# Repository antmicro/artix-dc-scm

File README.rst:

============
Artix DC-SCM
============

Copyright (c) 2020-2021 `Antmicro <https://www.antmicro.com>`_

.. image:: https://img.shields.io/badge/View%20on-Antmicro%20Open%20Source%20Portal-332d37?style=flat-square
   :target: https://opensource.antmicro.com/projects/artix-dc-scm 

.. figure:: img/artix-dc-scm.jpg

Overview
--------

This repository contains design files for an open-source Baseboard Management Controller (BMC) module based on the Xilinx Artix-7 FPGA family, designed in accordance with the Data Center Secure Control Module (DC-SCM) specification of Open Compute Project (OCP).

The design files were prepared in KiCad.
This design is complete and now undergoing bringup.

Repository structure
--------------------

The main repository directory contains KiCad PCB project files, a LICENSE and README.
The remaining files are stored in the following directories:

* ``lib`` - contains the component libraries
* ``img`` - contains graphics for this README

Key Features
------------

* Artix-7 FPGA - XC7A100T-FGG484
* DC-SCI standard 168-pin 4C+ edge connector
* On-board DDR3 DRAM (AS4C256M16D3) and eMMC (MTFC16GAPALNA-AIT)
* 4x SPI FLASH memory
* Gigabit Ethernet over KSZ9031RNXCA PHY
* JTAG connector
* Host and client USB (over USB3300-EZK-TR PHY)
* M.2 NVMe interface
* 13x I2C buses, 4x I3C buses
* 2x UART 
* SPI connector
* RoT module connector
* TPM SPI connector

Block diagram
-------------

.. figure:: img/artix-dc-scm-diagram.png

License
=======

`Apache-2.0 <LICENSE>`_

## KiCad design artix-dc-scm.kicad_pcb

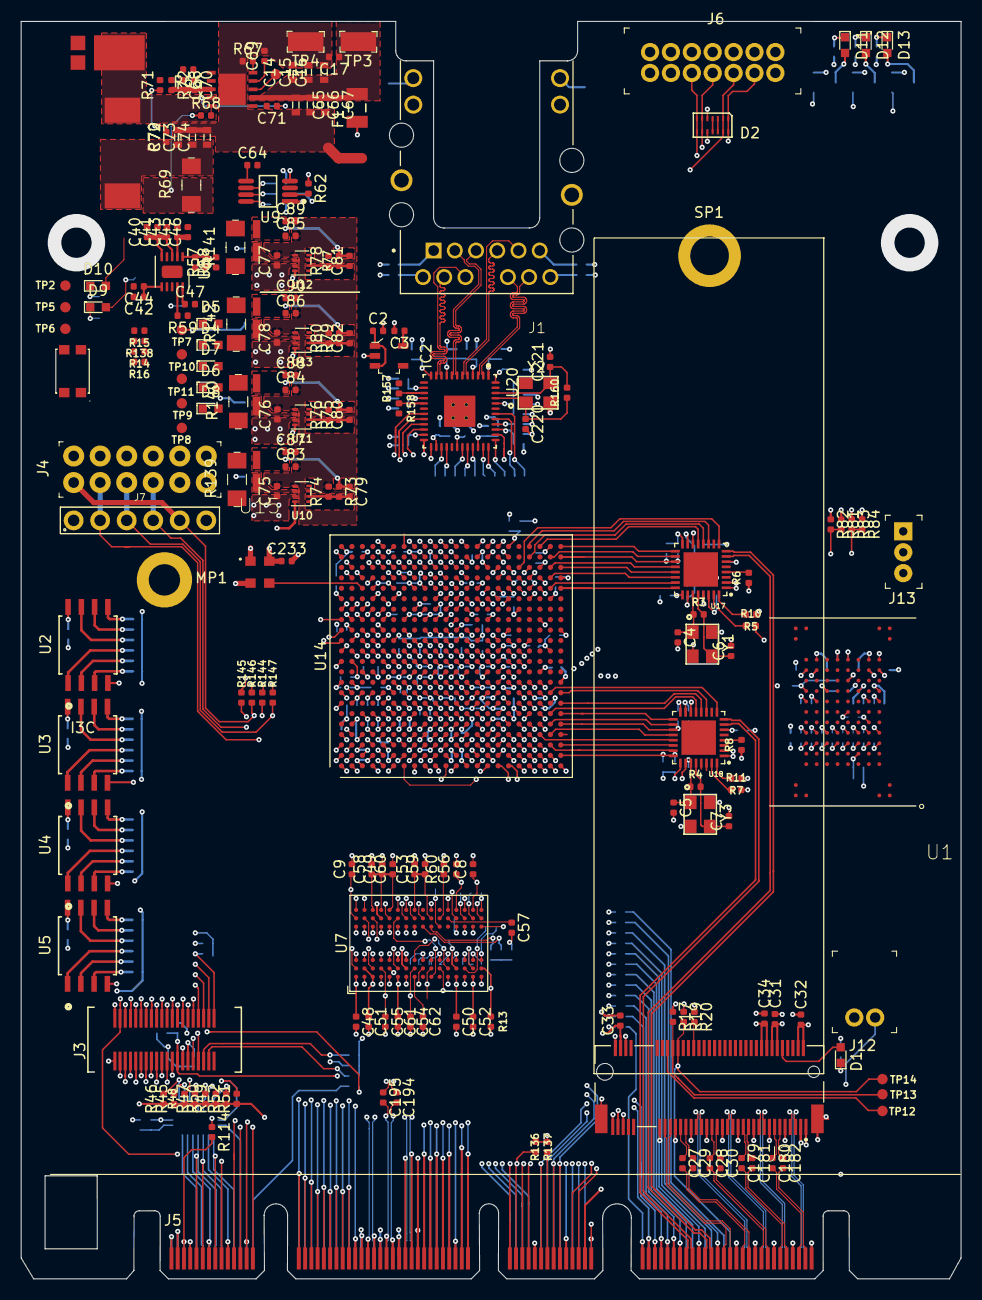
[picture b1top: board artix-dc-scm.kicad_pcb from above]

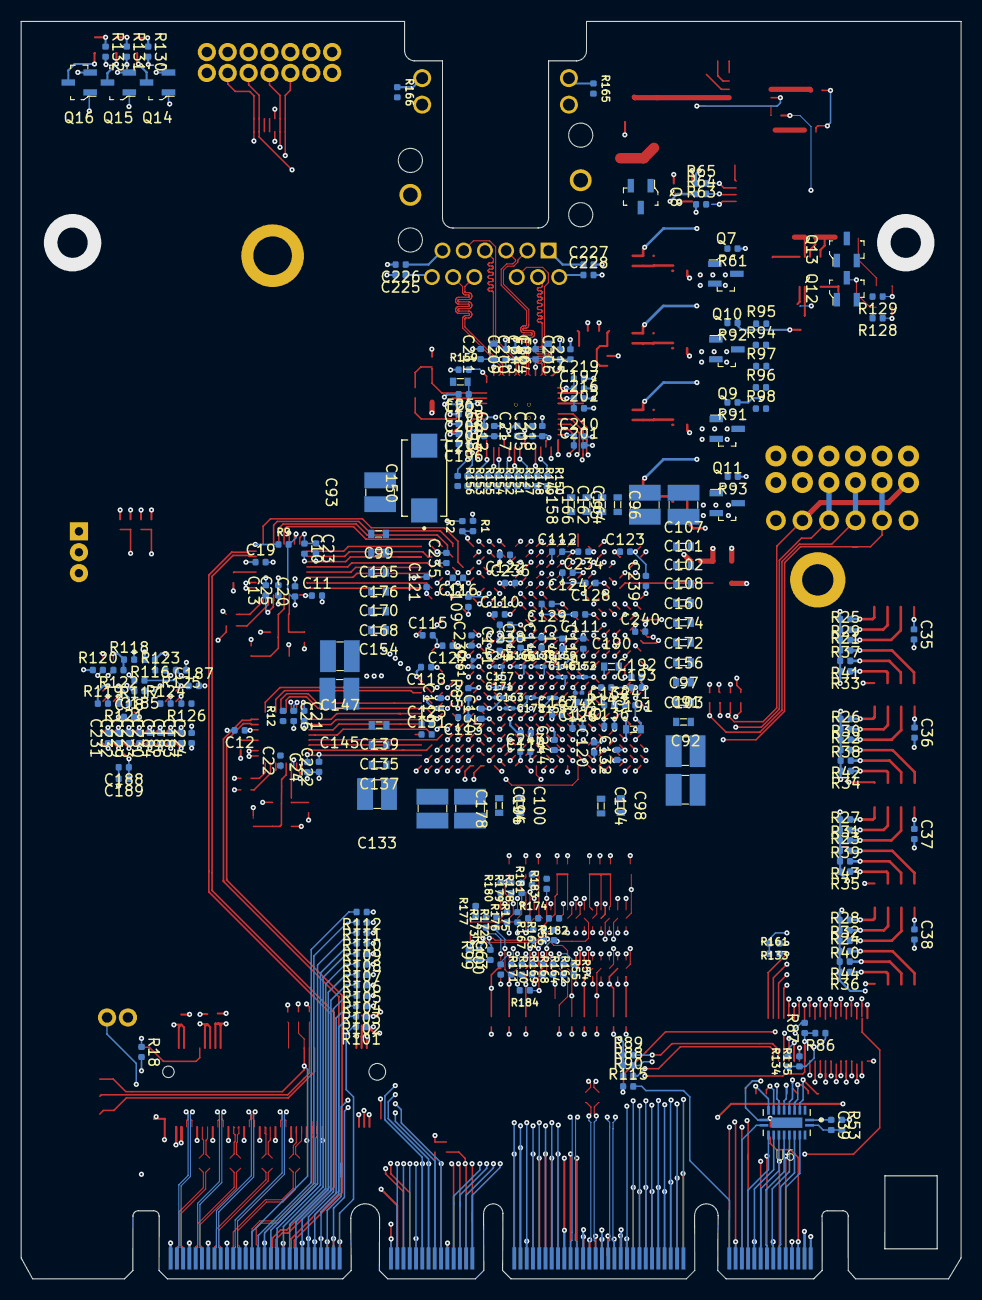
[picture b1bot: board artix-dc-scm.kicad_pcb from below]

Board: 8 copper layers, 90.0 x 120.4 mm, 502 parts (293 on the bottom side), 427 nets.

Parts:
C1: C_1n_0402; 0402-res
C2, C3: C_1u_0402; 0402-cap
C4, C5, C6, C7: C_12p_0402; 0402-cap
C8, C9, C35, C36, C37, C38, C49, C50, C51, C52, C53, C54, C55, C56, C58, C59, C60, C61, C109, C110, C111, C112, C113, C114, C115, C116, C117, C118, C119, C120, C121, C122, C123, C124, C125, C126, C127, C128, C129, C130, C131, C132, C140, C141, C143, C144, C148, C167, C197, C201, C202, C204, C205, C234, C235, C236, C237, C238, C239, C240, C243, C244: C_470n_0402; 0402-cap
C10, C11, C12, C13, C18, C19, C20, C21, C22, C24, C25, C26, C27, C28, C29, C30, C39, C42, C44, C45, C46, C57, C62, C63, C71, C134, C136, C179, C180, C181, C182, C186, C187, C189, C192, C193, C194, C195, C203, C223, C224, C225, C226, C227, C228, C229, C230, C231, C232, C233, C241: C_100n_0402; 0402-cap
C14, C15, C16: C_10u_25V_0603; 0603-cap
C17: C_100n_0402_16V; 0402-cap
C23, C48, C188, C196, C198, C199, C200, C206, C222: C_4u7_0402; 0402-cap
C31, C32, C33, C34, C40, C41, C43, C47, C75, C76, C77, C78, C83, C84, C85, C86, C87, C88, C89, C90: C_10u_0402; 0402-cap
C64, C69, C207, C208, C209, C210, C211, C212, C213, C214, C215, C216, C217, C218, C219: C_10n_0402; 0402-cap
C65, C66, C67: C_2u2_0603_25V; 0603-cap
C68: C_4n7_0402; 0402-cap
C70: C_47p_0402; 0402-cap
C72, C73, C74: C_47u_0603; 0603-cap
C79, C80, C81, C82: C_120p_0402; 0402-res
C91, C92, C93, C94, C95, C96, C133, C147, C178: C_47u_1210; 1210-cap
C97, C98, C99, C100, C101, C102, C103, C104, C105, C106, C107, C108, C135, C137, C139, C154, C156, C158, C160, C162, C164, C166, C168, C170, C172, C174, C176, C190, C191: C_4u7_0603; 0603-cap
C138, C142, C146, C152, C153, C157, C159, C161, C163, C165, C171, C175, C242: C_470n_0402; 0201-res
C145: C_100u_1210; 1210-cap
C150: C_330u_KEMET_D; KEMET_D
C183, C184, C185: C_2u2_0402; 0402-cap
C220, C221: C_22p_0402; 0402-cap
D1: KP-1608CGCK; LED_0603
D2: TPD6E05U06
D3: PDS760-13
D4, D5, D6, D7, D8, D9, D10, D11, D12, D13: LG_L29K-G2J1-24-Z; LED_0603
F1: 0466003.NR; 1206-Fuse-Littelfuse-0466-0-0-MFG
FB4, FB5, FB6: BLM18PG121SN1D; 0603-res
IC1: TPS54561; WSON-10_4x4
IC2: TLV73312PDBVT; SOT-23-5
J1: L834-1G1T-S7; BEL_L834-1G1T-S7
J2: 1-2199230-6
J3: 529910408
J4: M20-7830642; PinHeader_6x2_P2.54mm_Vertical
J5: SFF-TA-1002-4C+
J6: 0878311420; PinHeader_2x7_P2mm_Drill1mm
J7: 61300611121
J12: S2B-PH-K-S_LF__SN_; PinHeader_1x2_P2mm_Drill1mm_RA
J13: 62000311121
L1: WE_7447798720
L2, L3, L4, L5: IHLP1212AEERR47M11; IHLP-1212AE
MP1: PCB_Spacer_M2; 9774030243R
PROG_B1: KMR2; SW_SPST_4.2x2.8
Q7, Q8, Q9, Q10, Q11, Q12, Q13, Q14, Q15, Q16: 2N7002; SOT-23-3
R1, R2, R6, R8, R25, R26, R27, R28, R62, R63, R64, R65, R94, R95, R96, R97, R98, R128, R129, R130, R131, R132: R_1k_0402; 0402-res
R3, R4: R_1M5_0402; 0402-res
R5, R7: R_12k_0402; 0402-res
R9, R10, R11, R12, R14, R15, R16, R81, R82, R83, R84, R101, R102, R103, R104, R105, R106, R107, R108, R109, R110, R111, R112, R114, R115, R136, R137, R138, R144, R145, R146, R147, R161: R_0R_0402; 0402-res
R13, R21, R22, R23, R24, R85, R89, R90, R134, R135: R_4k7_0402; 0402-res
R17, R19, R20, R29, R30, R31, R32, R33, R34, R35, R36, R37, R38, R39, R40, R41, R42, R43, R44, R57, R58, R59, R61, R91, R92, R93, R116, R117, R118, R119, R120, R121, R122, R123, R124, R125, R126: R_10k_0402; 0402-res
R18: R_330R_0402; 0402-res
R45, R46, R47, R48, R49, R50, R51, R52: R_357k_0402; 0402-res
R53, R75: R_200k_0402; 0402-res
R54, R55, R56, R99, R100, R162, R163, R164, R167, R168, R169, R170, R171, R172, R173, R174, R175, R176, R177, R178, R179, R180, R181, R182, R183, R184: R_51R_0402; 0402-res
R60: R_240R_0402; 0402-res
R66: R_16k9_0402; 0402-res
R67: R_243k_0402; 0402-res
R68, R74, R76, R78, R80: R_100k_0402; 0402-res
R69, R139, R140, R141, R142: R_0R_1206; 1206-res
R70: R_49R9_0402; 0402-res
R71: R_53k6_0402; 0402-res
R72, R127, R148, R149, R150, R151, R152, R153, R154, R155, R156, R157, R158: R_10k2_0402; 0402-res
R73: R_453k_0402; 0402-res
R77: R_66k5_0402; 0402-res
R79: R_124k_0402; 0402-res
R86, R87, R143: R_100R_0402; 0402-res
R88: R_200R_0402; 0402-res
R133: R_2k2_0402; 0402-res
R159: R_12k1_0402; 0402-res
R160: R_1M8_0402; 0402-res
R165, R166: R_220R_0402; 0402-res
SP1: 9774025151
TP1, TP2, TP5, TP6, TP7, TP8, TP9, TP10, TP11, TP12, TP13, TP14: TP_SMD1MM; Testpoint_smd_1mm
TP3, TP4: RCW-0C; PROBE_PAD_1206
U1: MTFC16GAPALNA-AIT; BGA100CP100_17X10_1800X1400X140B46N
U2, U3, U4, U5: W25Q32JVSSIQ_TR; W25Q32JVSSIQ
U6: NVT2008DQ,115; QFN50P250X450X100-21N
U7: AS4C256M16D3; BGA-96_9.0x13.0mm_Layout2x3x16_P0.8mm
U8: TPS51200DRC; VSON-10-1EP_3x3mm
U9: LM3881MME_NOPB; VSSOP8-Texas_Instruments-DGK0008A
U10, U11, U12, U13: TPS62823DLCT; QFN-8_2x1mm
U14: XC7A100T-FGG484; Xilinx_FGG484
U15: AMJMEFB-100.0000T; AMJMEFB
U17, U18: USB3300-EZK-TR; QFN50P500X500X100-33N
U20: KSZ9031RNXCA; QFN-48-Microchip-QFN77-48LD-PL-2
Y1, Y3: TSX-3225; KX-7
Y2: ABM8G-25.000MHZ-18-D2Y-T; KX-7

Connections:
3V0_BAT: J5.B41, J12.1
/DDR3/DDR3_VTT: C40.1, C41.1, C43.1, R54.2, R55.2, R56.2, R162.2, R163.2, R164.2, R167.2, R168.2, R169.2, R170.2, R171.2, R172.2, R173.2, R174.2, R175.2, R176.2, R177.2, R178.2, R179.2, R180.2, R181.2, R182.2, R183.2, R184.2, U8.3, U8.5
/Ethernet/AVDDH: C206.1, C211.1, C215.1, FB4.2, U20.1, U20.12
/Ethernet/AVDDL: C200.1, C204.1, C209.1, C213.1, FB6.1, U20.4, U20.9
/Ethernet/AVDDL_PLL: C199.1, C203.1, C208.1, FB5.1, U20.44
/Ethernet/ETH1_N: J1.10, U20.3
/Ethernet/ETH1_P: J1.11, U20.2
/Ethernet/ETH2_N: J1.5, U20.6
/Ethernet/ETH2_P: J1.4, U20.5
/Ethernet/ETH3_N: J1.2, U20.8
/Ethernet/ETH3_P: J1.3, U20.7
/Ethernet/ETH4_N: J1.9, U20.11
/Ethernet/ETH4_P: J1.8, U20.10
/Ethernet/ETH_LED1: R157.1, U20.15
/Ethernet/ETH_LED2: R158.1, U20.17
/Interfaces/1V0_EN: C39.2, R53.2, U6.2, U6.20
/Interfaces/PCIE_BMC_TX_C_N: C194.1, U14.A4
/Interfaces/PCIE_BMC_TX_C_P: C195.1, U14.B4
/PCIe-connector/NVME_LED: D1.2, J2.10
/PCIe-connector/PCIE_HPM_TX0_C_N: C29.1, J2.47
/PCIe-connector/PCIE_HPM_TX0_C_P: C27.1, J2.49
/PCIe-connector/PCIE_HPM_TX1_C_N: C30.1, J2.35
/PCIe-connector/PCIE_HPM_TX1_C_P: C28.1, J2.37
/PCIe-connector/PCIE_HPM_TX2_C_N: C181.1, J2.23
/PCIe-connector/PCIE_HPM_TX2_C_P: C179.1, J2.25
/PCIe-connector/PCIE_HPM_TX3_C_N: C182.1, J2.11
/PCIe-connector/PCIE_HPM_TX3_C_P: C180.1, J2.13
/Power supply/1V0_PG: Q7.1, R61.2, U12.8
/Power supply/1V8_PG: Q9.1, R91.2, U11.8
/Power supply/1V35_PG: Q10.1, R92.2, U13.8
/Power supply/2V5_PG: Q11.1, R93.2
/Power supply/PWR_EN: Q8.1, R62.2, U9.2
/Power supply/VCCAUX_EN: R15.2, R64.2, U9.7
/Power supply/VCCINT_EN: R16.2, R63.2, U9.8
/Power supply/VCCIO_EN: R14.2, R65.2, R138.2, U9.6
CHASI#: J5.A54, R110.2
CHASI#_R: R110.1, U14.Y3
DBP_PRDY_N: J5.A50, R106.2
DBP_PRDY_N_R: R106.1, U14.W2
DBP_PREQ_N: J5.A49, R105.2
DBP_PREQ_N_R: R105.1, U14.V2
DDR3_A0: R168.1, U7.N3, U14.M2
DDR3_A1: R175.1, U7.P7, U14.M5
DDR3_A2: R169.1, U7.P3, U14.M3
DDR3_A3: R167.1, U7.N2, U14.M1
DDR3_A4: R178.1, U7.P8, U14.L6
DDR3_A5: R172.1, U7.P2, U14.P1
DDR3_A6: R179.1, U7.R8, U14.N3
DDR3_A7: R170.1, U7.R2, U14.N2
DDR3_A8: R180.1, U7.T8, U14.M6
DDR3_A9: R171.1, U7.R3, U14.R1
DDR3_A10: R183.1, U7.L7, U14.L5
DDR3_A11: R176.1, U7.R7, U14.N5
DDR3_A12: R174.1, U7.N7, U14.N4
DDR3_A13: R173.1, U7.T3, U14.P2
DDR3_A14: R177.1, U7.T7, U14.P6
DDR3_BA0: R163.1, U7.M2, U14.L3
DDR3_BA1: R181.1, U7.N8, U14.K6
DDR3_BA2: R164.1, U7.M3, U14.L4
DDR3_CAS: R55.1, U7.K3, U14.K3
DDR3_CKE: R182.1, U7.K9, U14.J6
DDR3_CLK_N: R100.2, U7.K7, U14.P4
DDR3_CLK_P: R99.2, U7.J7, U14.P5
DDR3_CS: R184.1, U7.L2
DDR3_DM0: U7.E7, U14.G3
DDR3_DM1: U7.D3, U14.F1
DDR3_DQ0: U7.E3, U14.G2
DDR3_DQ1: U7.F7, U14.H4
DDR3_DQ2: U7.F2, U14.H5
DDR3_DQ3: U7.F8, U14.J1
DDR3_DQ4: U7.H3, U14.K1
DDR3_DQ5: U7.H8, U14.H3
DDR3_DQ6: U7.G2, U14.H2
DDR3_DQ7: U7.H7, U14.J5
DDR3_DQ8: U7.D7, U14.E3
DDR3_DQ9: U7.C3, U14.B2
DDR3_DQ10: U7.C8, U14.F3
DDR3_DQ11: U7.C2, U14.D2
DDR3_DQ12: U7.A7, U14.C2
DDR3_DQ13: U7.A2, U14.A1
DDR3_DQ14: U7.B8, U14.E2
DDR3_DQ15: U7.A3, U14.B1
DDR3_DQS0_N: U7.G3, U14.J2
DDR3_DQS0_P: U7.F3, U14.K2
DDR3_DQS1_N: U7.B7, U14.D1
DDR3_DQS1_P: U7.C7, U14.E1
DDR3_ODT: R56.1, U7.K1, U14.K4
DDR3_RAS: R54.1, U7.J3, U14.J4
DDR3_RESET: R13.1, U7.T2, U14.G1
DDR3_VREF: C42.1, C44.1, C57.1, C62.1, U7.H1, U7.M8, U8.6
DDR3_WE: R162.1, U7.L3, U14.L1
DONE: Q13.1, R88.2, TP2.1, U14.G11
ESPI_ALERT_N: J5.B3, U14.H18
ESPI_CLK: J5.B1, U14.L18
ESPI_CS0_N: J5.B2, U14.K18
ESPI_CS1_N: J5.B9, U14.G15
ESPI_IO0: J5.B5, U14.K17
ESPI_IO1: J5.B6, U14.M16
ESPI_IO2: J5.B7, U14.K16
ESPI_IO3: J5.B8, U14.L16
ESPI_RESET_N: J5.B4, U14.M17
ETH_INT_N: U14.N20, U20.38
ETH_MDC: R154.1, U14.N22, U20.36
ETH_MDIO: R155.1, U14.M20, U20.37
ETH_~RESET: R156.1, U14.N18, U20.42
GCLK100: U14.C18, U15.3
GND: C1.2, C2.2, C3.2, C4.2, C5.2, C6.2, C7.2, C8.2, C9.2, C10.2, C11.2, C12.2, C13.2, C14.2, C15.2, C16.2, C17.2, C18.2, C19.2, C20.2, C21.2, C22.2, C23.2, C24.2, C25.2, C26.2, C31.2, C32.2, C33.2, C34.2, C35.2, C36.2, C37.2, C38.2, C39.1, C40.2, C41.2, C42.2, C43.2, C44.2, C45.2, C46.2, C47.2, C48.2, C49.2, C50.2, C51.2, C52.2, C53.2, C54.2, C55.2, C56.2, C57.2, C58.2, C59.2, C60.2, C61.2, C62.2, C63.1, C64.2, C65.2, C66.2, C67.2, C68.2, C69.2, C70.2, C72.2, C73.2, C74.2, C75.2, C76.2, C77.2, C78.2, C83.2, C84.2, C85.2, C86.2, C87.2, C88.2, C89.2, C90.2, C91.2, C92.2, C93.2, C94.2, C95.2, C96.2, C97.2, C98.2, C99.2, C100.2, C101.2, C102.2, C103.2, C104.2, C105.2, C106.2, C107.2, C108.2, C109.2, C110.2, C111.2, C112.2, C113.2, C114.2, C115.2, C116.2, C117.2, C118.2, C119.2, C120.2, C121.2, C122.2, C123.2, C124.2, C125.2, C126.2, C127.2, C128.2, C129.2, C130.2, C131.2, C132.2, C133.2, C134.2, C135.2, C136.2, C137.2, C138.2, C139.2, C140.2, C141.2, C142.2, C143.2, C144.2, C145.2, C146.2, C147.2, C148.2, C150.2, C152.2, C153.2, C154.2, C156.2, C157.2, C158.2, C159.2, C160.2, C161.2, C162.2, C163.2, C164.2, C165.2, C166.2, C167.2, C168.2, C170.2, C171.2, C172.2, C174.2, C175.2, C176.2, C178.2, C183.2, C184.2, C185.2, C186.2, C187.2, C188.2, C189.2, C190.2, C191.2, C192.2, C193.2, C196.2, C197.2, C198.2, C199.2, C200.2, C201.2, C202.2, C203.2, C204.2, C205.2, C206.2, C207.2, C208.2, C209.2, C210.2, C211.2, C212.2, C213.2, C214.2, C215.2, C216.2, C217.2, C218.2, C219.2, C220.2, C221.2, C222.2, C223.2, C224.2, C225.2, C226.2, C227.2, C228.2, C229.2, C230.2, C231.2, C232.2, C233.2, C234.2, C235.2, C236.2, C237.2, C238.2, C239.2, C240.2, C241.2, C242.2, C243.2, C244.2, D2.5, D2.10, D3.A, IC1.8, IC1.11, IC2.2, J1.13, J1.15, J1.S1, J1.S2, J2.1, J2.3, J2.9, J2.15, J2.21, J2.27, J2.33, J2.39, J2.45, J2.51, J2.57, J2.71, J2.73, J2.75, J2.SH1, J2.SH2, J3.1, J4.5, J4.11, J5.A11, J5.A14, J5.A17, J5.A20, J5.A33, J5.A42, J5.A58, J5.A61, J5.A64, J5.A67, J5.A70, J5.B10, J5.B17, J5.B26, J5.B33, J5.B38, J5.B49, J5.B52, J5.B55, J5.B58, J5.B61, J5.B64, J5.B67, J5.B70, J5.OA3, J5.OA4, J5.OA13, J5.OB4, J5.OB7, J5.OB10, J6.1, J6.3, J6.5, J6.7, J6.9, J6.11, J6.13, J7.6, J12.2, J13.3, PROG_B1.2, Q7.2, Q8.2, Q9.2, Q10.2, Q11.2, Q12.2, Q13.2, Q14.2, Q15.2, Q16.2, R2.2, R5.1, R7.1, R13.2, R57.1, R60.2, R67.1, R72.2, R74.2, R76.2, R78.2, R80.2, R82.1, R84.1, R87.2, R159.1, TP4.1, U1.G2, U1.G3, U1.G4, U1.G5, U1.G6, U1.G7, U1.G8, U1.G9, U1.J5, U2.4, U3.4, U4.4, U5.4, U6.1, U7.A9, U7.B1, U7.B3, U7.B9, U7.D1, U7.D8, U7.E1, U7.E2, U7.E8, U7.F9, U7.G1, U7.G8, U7.G9, U7.J2, U7.J8, U7.M1, U7.M9, U7.P1, U7.P9, U7.T1, U7.T9, U8.4, U8.8, U8.11, U9.3, U10.3, U10.5, U11.3, U11.5, U12.3, U12.5, U13.3, U13.5, U14.A2, U14.A3, U14.A5, U14.A7, U14.A9, U14.A11, U14.A12, U14.A22, U14.AA2, U14.AA12, U14.AA22, U14.AB9, U14.AB19, U14.B3, U14.B12, U14.B19, U14.C3, U14.C6, U14.C10, U14.C12, U14.C16, U14.D3, U14.D4, U14.D8, U14.D12, U14.D13, U14.E4, U14.E5, U14.E7, U14.E9, U14.E11, U14.E20, U14.F5, U14.F11, U14.F17, U14.G5, U14.G6, U14.G7, U14.G8, U14.G9, U14.G10, U14.G12, U14.G14, U14.H1, U14.H7, U14.H9, U14.H11, U14.H21, U14.J8, U14.J10, U14.J12, U14.J18, U14.K5, U14.K7, U14.K9, U14.K11, U14.K15, U14.L2, U14.L8, U14.L9, U14.L10, U14.L22, U14.M7, U14.M9, U14.M10, U14.M11, U14.M19, U14.N6, U14.N8, U14.N9, U14.N10, U14.N16, U14.P3, U14.P7, U14.P9, U14.P11, U14.P13, U14.R8, U14.R10, U14.R12, U14.R20, U14.T7, U14.T9, U14.T11, U14.T17, U14.U4, U14.U14, U14.V1, U14.V11, U14.V21, U14.W8, U14.W18, U14.Y5, U14.Y15, U15.2, U17.1, U17.2, U17.33, U18.1, U18.2, U18.33, U20.29, U20.49, Y1.2, Y1.4, Y2.2, Y2.4, Y3.2, Y3.4
HPM_FW_RECOVERY: J5.A43, R101.2
HPM_FW_RECOVERY_R: R101.1, U14.U3
HPM_STBY_RST_N: J5.A46, R102.2
HPM_STBY_RST_N_R: R102.1, U14.U1
I2C[0]_SCL: J5.A1, U14.J16
I2C[0]_SDA: J5.A2, U14.J15
I2C[1]_SCL: J5.A3, U14.L15
I2C[1]_SDA: J5.A4, U14.M15
I2C[2]_SCL: J5.A5, U14.L14
I2C[2]_SDA: J5.A6, U14.J14
I2C[3]_SCL: J5.A7, U14.K14
I2C[3]_SDA: J5.A8, U14.M13
I2C[4]_SCL: J5.A9, U14.K13
I2C[4]_SDA: J5.A10, U14.L13
I2C[5]_SCL: J5.A21, U14.N13
I2C[5]_SDA: J5.A22, U14.N14
I2C[6]_SCL: J5.A23, U14.H13
I2C[6]_SDA: J5.A24, U14.G13
I2C[7]_SCL: J5.A25, U14.F13
I2C[7]_SDA: J5.A26, U14.E13
I2C[8]_SCL: J5.A27, U14.C13
I2C[8]_SDA: J5.A28, U14.C14
I2C[9]_SCL: J5.A29, U14.T5
I2C[9]_SDA: J5.A30, U14.T6
I2C[10]_SCL: J5.A31, U14.U6
I2C[10]_SDA: J5.A32, U14.W6
I2C[11]_SCL: J5.A38, U14.W7
I2C[11]_SDA: J5.A39, U14.W9
I2C[12]_SCL: J5.A40, U14.V8
I2C[12]_SDA: J5.A41, U14.V9
I3C[0]_SCL: J5.OA5, U6.18
I3C[0]_SCL_3V3: R46.2, U6.3, U14.A21
I3C[0]_SDA: J5.OA6, U6.17
I3C[0]_SDA_3V3: R45.2, U6.4, U14.B20
I3C[1]_SCL: J5.OA7, U6.16
I3C[1]_SCL_3V3: R48.2, U6.5, U14.D20
I3C[1]_SDA: J5.OA8, U6.15
I3C[1]_SDA_3V3: R47.2, U6.6, U14.F20
I3C[2]_SCL: J5.OA9, U6.14
I3C[2]_SCL_3V3: R50.2, U6.7, U14.C19
I3C[2]_SDA: J5.OA10, U6.13
I3C[2]_SDA_3V3: R49.2, U6.8, U14.F19
I3C[3]_SCL: J5.OA11, U6.12
I3C[3]_SCL_3V3: R52.2, U6.9, U14.D19
I3C[3]_SDA: J5.OA12, U6.11
I3C[3]_SDA_3V3: R51.2, U6.10, U14.F18
INIT: J3.19, Q12.1, R90.2, TP5.1, U14.U12
IRQ_N: J5.A56, R112.2
IRQ_N_R: R112.1, U14.AB1
JTAG_TCK: D2.13, J5.A34, J6.6, U14.V12
JTAG_TDI: D2.8, J5.A36, J6.10, U14.R13
JTAG_TDO: D2.9, J5.A37, J6.8, U14.U13
JTAG_TMS: D2.14, J5.A35, J6.4, U14.T13
MMC_CLK: R116.2, U1.P6, U14.Y18
MMC_CMD: R118.2, U1.P5, U14.Y19
MMC_DAT0: R119.2, U1.K2, U14.P17
MMC_DAT1: R120.2, U1.N2, U14.W17
MMC_DAT2: R121.2, U1.K3, U14.R18
MMC_DAT3: R122.2, U1.N3, U14.V18
MMC_DAT4: R123.2, U1.N8, U14.U18
MMC_DAT5: R124.2, U1.K8, U14.U17
MMC_DAT6: R125.2, U1.N9, U14.T18
MMC_DAT7: R126.2, U1.K9, U14.R17
MMC_RSTN: R117.2, U1.M5, U14.V19
MODE0: R81.2, R82.2, U14.U11
MODE1: R83.2, R84.2, U14.U10
MODE2: J13.2, U14.U9
NCSI_CLK: J5.B18, U14.B13
NCSI_CRS_DV: J5.B19, U14.A14
NCSI_RXD0: J5.B24, U14.A15
NCSI_RXD1: J5.B25, U14.B15
NCSI_RXER: J5.B23, U14.C15
NCSI_TXD0: J5.B21, U14.D14
NCSI_TXD1: J5.B22, U14.E14
NCSI_TXEN: J5.B20, U14.A13
unnamed: C1.1, R57.2, R58.2, U8.1
unnamed: C4.1, R3.1, U17.27, Y1.1
unnamed: C5.1, R4.1, U18.27, Y3.1
unnamed: C6.1, R3.2, U17.28, Y1.3
unnamed: C7.1, R4.2, U18.28, Y3.3
unnamed: C20.1, R9.2, U17.15, U17.26
unnamed: C22.1, U18.29
unnamed: C25.1, U17.29
unnamed: C26.1, R12.2, U18.15, U18.26
unnamed: C63.2, R99.1, R100.1
unnamed: C64.1, U9.5
unnamed: C68.1, R66.2
unnamed: C69.1, IC1.4
unnamed: C70.1, IC1.7, R66.1
unnamed: C71.1, D3.C, IC1.9, L1.1
unnamed: C71.2, IC1.1
unnamed: C72.1, C73.1, C74.1, L1.2, R69.2, R70.1
unnamed: C79.1, C83.1, C87.1, L2.2, R73.1, R139.2, TP8.1
unnamed: C79.2, R73.2, R74.1, U10.2
unnamed: C80.1, C84.1, C88.1, L3.2, R75.1, R140.2, TP9.1
unnamed: C80.2, R75.2, R76.1, U11.2
unnamed: C81.1, C85.1, C89.1, L4.2, R77.1, R141.2, TP10.1
unnamed: C81.2, R77.2, R78.1, U12.2
unnamed: C82.1, C86.1, C90.1, L5.2, R79.1, R142.2, TP11.1
unnamed: C82.2, R79.2, R80.1, U13.2
unnamed: C188.1, C189.1, U1.E4
unnamed: C220.1, R160.1, U20.45, Y2.1
unnamed: C221.1, R160.2, U20.46, Y2.3
unnamed: C225.1, J1.12
unnamed: C226.1, J1.6
unnamed: C227.1, J1.1
unnamed: C228.1, J1.7
unnamed: D1.1, R18.2
unnamed: D4.1, R94.1
unnamed: D4.2, Q7.3
unnamed: D5.1, R95.1
unnamed: D5.2, Q8.3
unnamed: D6.1, R96.1
unnamed: D6.2, Q9.3
unnamed: D7.1, R97.1
unnamed: D7.2, Q10.3
unnamed: D8.1, R98.1
unnamed: D8.2, Q11.3
unnamed: D9.1, R128.1
unnamed: D9.2, Q12.3
unnamed: D10.1, R129.1
unnamed: D10.2, Q13.3
unnamed: D11.1, R130.1
unnamed: D11.2, Q14.3
unnamed: D12.1, R131.1
unnamed: D12.2, Q15.3
unnamed: D13.1, R132.1
unnamed: D13.2, Q16.3
unnamed: IC1.3, TP1.1
unnamed: IC1.5, R67.2
unnamed: IC1.6, R71.2, R72.1
unnamed: J1.14, R165.1
unnamed: J1.16, R166.1
unnamed: J2.44, R20.2
unnamed: J2.52, R17.2, TP13.1
unnamed: J2.54, TP12.1
unnamed: J5.B35, R136.1
unnamed: L2.1, U10.6
unnamed: L3.1, U11.6
unnamed: L4.1, U12.6
unnamed: L5.1, U13.6
unnamed: R5.2, U17.32
unnamed: R6.2, U17.4
unnamed: R7.2, U18.32
unnamed: R8.2, U18.4
unnamed: R10.1, U17.31
unnamed: R11.1, U18.31
unnamed: R14.1, U10.1
unnamed: R15.1, U11.1
unnamed: R16.1, U12.1
unnamed: R59.2, U8.9
unnamed: R60.1, U7.L8
unnamed: R70.2, R71.1
unnamed: R85.2, U14.U8
unnamed: R133.2, R161.1, U14.T19
unnamed: R138.1, U13.1
unnamed: R143.2, U14.F8
unnamed: R159.2, U20.48
unnamed: U1.H2, U1.H9, U1.L3, U1.L8, U1.M4, U1.M7, U1.P2, U1.P9
P12V_AUX: F1.1, J5.OA1, J5.OA2, J5.OB1, J5.OB2
PCIE_BMC_CLK_100_N: J5.A13, U14.E6
PCIE_BMC_CLK_100_P: J5.A12, U14.F6
PCIE_BMC_RX_N: J5.A19, U14.A8
PCIE_BMC_RX_P: J5.A18, U14.B8
PCIE_BMC_TX_N: C194.2, J5.A16
PCIE_BMC_TX_P: C195.2, J5.A15
PCIE_HPM_CLK_N: J2.53, J5.B57
PCIE_HPM_CLK_P: J2.55, J5.B56
PCIE_HPM_RX[0]_N: J2.41, J5.A60
PCIE_HPM_RX[0]_P: J2.43, J5.A59
PCIE_HPM_RX[1]_N: J2.29, J5.A63
PCIE_HPM_RX[1]_P: J2.31, J5.A62
PCIE_HPM_RX[2]_N: J2.17, J5.A66
PCIE_HPM_RX[2]_P: J2.19, J5.A65
PCIE_HPM_RX[3]_N: J2.5, J5.A69
PCIE_HPM_RX[3]_P: J2.7, J5.A68
PCIE_HPM_TX[0]_N: C29.2, J5.B60
PCIE_HPM_TX[0]_P: C27.2, J5.B59
PCIE_HPM_TX[1]_N: C30.2, J5.B63
PCIE_HPM_TX[1]_P: C28.2, J5.B62
PCIE_HPM_TX[2]_N: C181.2, J5.B66
PCIE_HPM_TX[2]_P: C179.2, J5.B65
PCIE_HPM_TX[3]_N: C182.2, J5.B69
PCIE_HPM_TX[3]_P: C180.2, J5.B68
PROGRAM: J3.18, PROG_B1.1, PROG_B1.3, R89.2, TP6.1, U14.N12
PRSNT0_N: J5.OB3, R114.2
PRSNT0_N_R: R114.1, U14.E21
PRSNT1_N: J2.50, J5.A57, R19.2, TP14.1
PUDC_B: R1.2, R2.1, U14.U22
PWR_GOOD: IC1.10, R68.2
QSPI0_CLK: J3.7, J5.B11
QSPI0_CS0_N: J3.8, J5.B12
QSPI0_CS1_N: J3.22, J5.B42
QSPI0_D0: J3.9, J5.B13
QSPI0_D1: J3.10, J5.B14
QSPI0_D2: J3.11, J5.B15
QSPI0_D3: J3.12, J5.B16
QSPI1_CLK: J5.B43, U14.R4
QSPI1_CS0_N: J5.B44, U14.R2
QSPI1_D0: J5.B45, U14.R3
QSPI1_D1: J5.B46, U14.T4
QSPI1_D2: J5.B47, U14.T3
QSPI1_D3: J5.B48, U14.T1
QSPIA1_CS_N: J3.4, R24.2, U5.1
QSPIA1_D0: J3.6, R32.1, U5.5
QSPIA1_D1: J3.3, R44.1, U5.2
QSPIA1_D2: J3.2, R36.1, U5.3
QSPIA1_D3: J3.5, R40.1, U5.7
QSPIA2_CS_N: J3.25, R23.2, U4.1
QSPIA2_D0: J3.28, R31.1, U4.5
QSPIA2_D1: J3.24, R43.1, U4.2
QSPIA2_D2: J3.23, R35.1, U4.3
QSPIA2_D3: J3.26, R39.1, U4.7
QSPIA_CLK: J3.27, R27.2, R28.2, U4.6, U5.6
QSPIB1_CS_N: J3.31, R22.2, U3.1
QSPIB1_D0: J3.33, R30.1, U3.5
QSPIB1_D1: J3.30, R42.1, U3.2
QSPIB1_D2: J3.29, R34.1, U3.3
QSPIB1_D3: J3.32, R38.1, U3.7
QSPIB2_CS_N: J3.36, R21.2, U2.1
QSPIB2_D0: J3.39, R29.1, U2.5
QSPIB2_D1: J3.35, R41.1, U2.2
QSPIB2_D2: J3.34, R33.1, U2.3
QSPIB2_D3: J3.37, R37.1, U2.7
QSPIB_CLK: J3.38, R25.2, R26.2, U2.6, U3.6
RGMII_REF_CLK: R153.1, U14.N19, U20.41
RGMII_RXD0: R127.1, U14.L20, U20.32
RGMII_RXD1: R148.1, U14.L21, U20.31
RGMII_RXD2: R149.1, U14.K21, U20.28
RGMII_RXD3: R150.1, U14.K22, U20.27
RGMII_RX_CLK: R152.1, U14.M21, U20.35
RGMII_RX_DV: R151.1, U14.M22, U20.33
RGMII_TXD0: U14.G20, U20.19
RGMII_TXD1: U14.H20, U20.20
RGMII_TXD2: U14.H22, U20.21
RGMII_TXD3: U14.J21, U20.22
RGMII_TX_CLK: U14.J22, U20.24
RGMII_TX_DV: U14.J20, U20.25
ROT_QSPI_CS_B: J3.40, R161.2
ROT_QSPI_DQ0: J3.17, U14.P22
ROT_QSPI_DQ1: J3.16, U14.R22
ROT_QSPI_DQ2: J3.15, R134.2, U14.P21
ROT_QSPI_DQ3: J3.14, R135.2, U14.R21
ROT_QSPI_SCK: J3.13, R86.2, R87.1, U14.L12
RST_PLTRST_BUF_N: J5.A51, R107.2
RST_PLTRST_BUF_N_R: R107.1, U14.W1
RSVD2: R136.2, R137.1, U14.Y7
RoT_CPU_RST_N: J5.A53, R109.2
RoT_CPU_RST_N_R: R109.1, U14.Y1
SGPIO0_CLK: J5.B30, R137.2, U14.W5
SGPIO0_DI: J5.B31, U14.W4
SGPIO0_DO: J5.B29, U14.V5
SGPIO0_LD: J5.B32, U14.V7
SGPIO1_DI: J5.B36, U14.Y8
SGPIO1_DO: J5.B34, U14.Y6
SGPIO1_LD: J5.B37, U14.Y9
SGPIO_INTR_N: J5.B40, U14.U7
SGPIO_RESET_N: J5.B39, U14.U5
SPARE0: J5.A55, R111.2
SPARE0_R: R111.1, U14.AA1
SPARE1: J5.A52, R108.2
SPARE1_R: R108.1, U14.Y2
SPI0_CLK: J4.4, J5.OB11, J7.4, R145.2
SPI0_CLK_R: R145.1, U14.E16
SPI0_CS_N: J4.1, J5.OB12, J7.5, R146.2
SPI0_CS_N_R: R146.1, U14.D16
SPI0_MISO: J4.3, J5.OB14, J7.3, R147.2
SPI0_MISO_R: R147.1, U14.B16
SPI0_MOSI: J4.2, J5.OB13, J7.2, R144.2
SPI0_MOSI_R: R144.1, U14.A16
SYS_PWRBTN_N: J5.A47, R103.2
SYS_PWRBTN_N_R: R103.1, U14.U2
SYS_PWROK: J5.A48, R104.2
SYS_PWROK_R: R104.1, U14.V3
UART0_SCM_RX: J5.OB9, U14.D17
UART0_SCM_TX: J5.OB8, U14.E17
UART1_SCM_RX: J5.OB6, U14.T21
UART1_SCM_TX: J5.OB5, U14.U21
ULPI1_CLKOUT: U14.W19, U17.14
ULPI1_DATA0: U14.AB18, U17.24
ULPI1_DATA1: U14.AA18, U17.23
ULPI1_DATA2: U14.AA19, U17.22
ULPI1_DATA3: U14.AB20, U17.21
ULPI1_DATA4: U14.AA20, U17.20
ULPI1_DATA5: U14.AB21, U17.19
ULPI1_DATA6: U14.AA21, U17.18
ULPI1_DATA7: U14.AB22, U17.17
ULPI1_DIR: U14.W21, U17.12
ULPI1_NXT: U14.W22, U17.11
ULPI1_RESET: U14.V20, U17.9
ULPI1_STP: U14.Y22, U17.13
ULPI2_CLKOUT: U14.V4, U18.14
ULPI2_DATA0: U14.AB2, U18.24
ULPI2_DATA1: U14.AA3, U18.23
ULPI2_DATA2: U14.AB3, U18.22
ULPI2_DATA3: U14.Y4, U18.21
ULPI2_DATA4: U14.AA4, U18.20
ULPI2_DATA5: U14.AB5, U18.19
ULPI2_DATA6: U14.AA5, U18.18
ULPI2_DATA7: U14.AB6, U18.17
ULPI2_DIR: U14.AB7, U18.12
ULPI2_NXT: U14.AB8, U18.11
ULPI2_RESET: U14.AA8, U18.9
ULPI2_STP: U14.AA6, U18.13
USB1_D_N: J5.B54, U17.8
USB1_D_P: J5.B53, U17.7
USB2_D_N: J5.B51, U18.8
USB2_D_P: J5.B50, U18.7
USR_LED0: Q14.1, U14.T20
USR_LED1: Q15.1, U14.U20
USR_LED2: Q16.1, U14.W20
VCC1V0: C134.1, C136.1, C138.1, C140.1, C142.1, C145.1, C147.1, C150.1, C152.1, C153.1, C154.1, C156.1, C157.1, C158.1, C159.1, C160.1, C161.1, C162.1, C163.1, C164.1, C165.1, C166.1, C167.1, C168.1, C170.1, C171.1, C172.1, C174.1, C175.1, C176.1, C190.1, R141.1, U6.19, U14.D6, U14.D10, U14.E8, U14.F7, U14.F9, U14.H8, U14.H10, U14.J7, U14.J9, U14.J11, U14.K8, U14.L7, U14.L11, U14.M8, U14.N7, U14.N11, U14.P8, U14.P10, U14.R7, U14.R9, U14.T8, U14.T10
VCC1V2: C3.1, C191.1, C192.1, C193.1, C196.1, C197.1, C201.1, C205.1, C210.1, C214.1, C217.1, C218.1, C219.1, C241.1, FB5.2, FB6.2, IC2.5, R143.1, U14.B5, U14.B7, U14.B9, U14.B11, U14.C4, U14.C8, U20.14, U20.23, U20.26, U20.30, U20.39
VCC1V8: C133.1, C135.1, C137.1, C139.1, C141.1, C143.1, C144.1, C146.1, C148.1, C242.1, R9.1, R12.1, R20.1, R140.1, U14.E12, U14.H12, U14.K10, U14.K12, U14.M12, U14.P12, U14.R11
VCC1V35: C8.1, C9.1, C45.1, C46.1, C48.1, C49.1, C50.1, C51.1, C52.1, C53.1, C54.1, C55.1, C56.1, C58.1, C59.1, C60.1, C61.1, C96.1, C102.1, C108.1, C114.1, C120.1, C126.1, C132.1, C243.1, C244.1, R58.1, R142.1, U7.A1, U7.A8, U7.B2, U7.C1, U7.C9, U7.D2, U7.D9, U7.E9, U7.F1, U7.G7, U7.H2, U7.H9, U7.K2, U7.K8, U7.N1, U7.N9, U7.R1, U7.R9, U8.2, U14.C1, U14.F2, U14.H6, U14.J3, U14.M4, U14.N1
VCC3V3: C2.1, C10.1, C11.1, C12.1, C13.1, C18.1, C19.1, C21.1, C23.1, C24.1, C31.1, C32.1, C33.1, C34.1, C35.1, C36.1, C37.1, C38.1, C47.1, C91.1, C92.1, C93.1, C94.1, C95.1, C97.1, C98.1, C99.1, C100.1, C101.1, C103.1, C104.1, C105.1, C106.1, C107.1, C109.1, C110.1, C111.1, C112.1, C113.1, C115.1, C116.1, C117.1, C118.1, C119.1, C121.1, C122.1, C123.1, C124.1, C125.1, C127.1, C128.1, C129.1, C130.1, C131.1, C178.1, C183.1, C184.1, C185.1, C186.1, C187.1, C198.1, C202.1, C207.1, C212.1, C216.1, C222.1, C223.1, C224.1, C229.1, C230.1, C231.1, C232.1, C233.1, C234.1, C235.1, C236.1, C237.1, C238.1, C239.1, C240.1, FB4.1, IC2.1, IC2.3, J2.2, J2.4, J2.12, J2.14, J2.16, J2.18, J2.70, J2.72, J2.74, J3.21, J4.6, J4.12, J6.2, J7.1, J13.1, R1.1, R10.2, R11.2, R17.1, R18.1, R19.1, R21.1, R22.1, R23.1, R24.1, R25.1, R26.1, R27.1, R28.1, R29.2, R30.2, R31.2, R32.2, R33.2, R34.2, R35.2, R36.2, R37.2, R38.2, R39.2, R40.2, R41.2, R42.2, R43.2, R44.2, R45.1, R46.1, R47.1, R48.1, R49.1, R50.1, R51.1, R52.1, R53.1, R59.1, R81.1, R83.1, R85.1, R86.1, R88.1, R89.1, R90.1, R94.2, R95.2, R96.2, R97.2, R98.2, R116.1, R117.1, R118.1, R119.1, R120.1, R121.1, R122.1, R123.1, R124.1, R125.1, R126.1, R127.2, R128.2, R129.2, R130.2, R131.2, R132.2, R133.1, R134.1, R135.1, R139.1, R148.2, R149.2, R150.2, R151.2, R152.2, R153.2, R154.2, R155.2, R156.2, R157.2, R158.2, U1.F2, U1.F3, U1.F4, U1.F5, U1.F6, U1.F7, U1.F8, U1.F9, U1.H3, U1.H8, U1.L2, U1.L4, U1.L7, U1.L9, U1.P3, U1.P8, U2.8, U3.8, U4.8, U5.8, U8.7, U8.10, U14.A17, U14.AA7, U14.AA17, U14.AB4, U14.AB14, U14.B14, U14.C21, U14.D18, U14.E15, U14.F12, U14.F22, U14.G19, U14.H16, U14.J13, U14.K20, U14.L17, U14.M14, U14.N21, U14.P18, U14.R5, U14.R15, U14.T2, U14.T12, U14.T22, U14.U19, U14.V6, U14.V16, U14.W3, U14.W13, U14.Y10, U14.Y20, U15.1, U15.4, U17.6, U17.16, U17.25, U17.30, U18.6, U18.16, U18.25, U18.30, U20.16, U20.34, U20.40
VCC5V0: C75.1, C76.1, C77.1, C78.1, R6.1, R8.1, R61.1, R62.1, R63.1, R64.1, R65.1, R68.1, R69.1, R91.1, R92.1, R93.1, TP7.1, U9.1, U9.4, U10.7, U11.7, U12.7, U13.7
VCC12V: C14.1, C15.1, C16.1, C17.1, C65.1, C66.1, C67.1, F1.2, IC1.2, TP3.1
VIRTUAL_RESEAT: J5.OA14, R115.2
VIRTUAL_RESEAT_R: R115.1, U14.E22

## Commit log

2020-12-11 Initial commit - moved interfaces from ECP5, replaced FPGA, done FPGA decoupling
2020-12-11 Changes to voltage regulators
2020-12-11 DDR3 sheet edits
2020-12-11 Minor changes to FPGA
2020-12-11 Added Xilinx JTAG connector
2020-12-11 Added FPGA connections
2020-12-11 FPGA supplies update
2020-12-12 Updated power sequencer
2020-12-12 Added TPM SPI connector
2020-12-12 Removed redundant VRs (2V5, 1V2)
2020-12-12 Initial component placement added (to be adjusted further)
2020-12-13 Removed inverters
2020-12-13 Minor fixes in component placement
2020-12-13 Neatened main sheet
2020-12-14 Update after designator unification
2020-12-14 Ethernet IC component placement done
2020-12-14 DDR3 PMIC initial placement done
2020-12-14 5V0 VR component placement done
2020-12-14 Fix outline
2020-12-14 Close PCB outline
2020-12-15 Added block diagram
2020-12-15 Added DDR3 and FLASH layout
2020-12-15 Updated board 3D models
2020-12-15 Added 3D vis
2020-12-15 Added M.2 connector layout
2020-12-15 Added interfaces layouts
2020-12-15 Changed PCIe connection
2020-12-15 Updated block diagram
2020-12-15 Add local component libraries
2020-12-15 Updated 3D vis
2020-12-15 README: minor fix
2020-12-16 Added VRs component placement, fix in 5V0 layout
2020-12-16 Removed DC connector
2020-12-16 Added PWR_EN optional pullup
2020-12-16 Added testpad footprint to libs
2020-12-16 Removed debug headers
2020-12-16 Added power sequencer component placement, minor fixes in schematics
2020-12-16 Component placement done
2020-12-16 Redone RGMII FPGA connection
2020-12-17 Improved FPGA signals connection (WIP)
2020-12-17 Improved DDR3 related connection (WIP)
2020-12-18 Updated RoT and FLASH connections
2020-12-18 Improved DDR3 to FPGA connections (WIP)
2020-12-18 DDR3 to FPGA connections finished
2020-12-21 Added eMMC
2020-12-22 Connected boot QSPI
2020-12-22 Swapped RAS and CAS connection
2020-12-22 Replaced PHY
2020-12-22 Boot QSPI fixes, added status LEDs
2020-12-23 FPGA related fixes, removed floating tags from Interfaces
2020-12-23 Fixes to PCIe connector
2020-12-23 Fixes after review (pin connections)
2020-12-23 Added USB client chip
2020-12-24 New ICs component placement, replaced RJ45
2020-12-24 Fixed PCIe x1 connection
2020-12-26 Reconnected DDR3
2020-12-26 Reconnected ethernet
2020-12-26 Reconnected USB
2020-12-26 Connected eMMC
2020-12-27 Reconnected interfaces
2020-12-28 Finished connecting to FPGA
2020-12-28 Added SPI connector
2020-12-28 Added local libs
2020-12-28 Updated libs
2020-12-28 Fix in libs
2020-12-28 Updated 3D vis and block diagram
2020-12-28 Update component libraries
2020-12-28 Update sheet titles, add PDF schematic
2020-12-28 Cleanup around Ethernet schematic
2020-12-28 Clean M.2 sheet
2020-12-28 RoT - cleanup
2020-12-28 Update PDF schematic
2020-12-28 Add simple stackup description
2020-12-28 Update naming convention for PCIe
2020-12-28 Add DRC for PCIe routing
2020-12-28 Add net labels to coupled PCIe lanes
2020-12-28 Add layout to M.2 PCIe
2020-12-28 Change M.2 description in README
2020-12-29 Specify eMMC model
2020-12-29 Add suggested MPS for ETH PHYs
2020-12-29 Add BMC PCIe net classes
2020-12-29 Define USB diff lanes
2020-12-29 Route low speed HPM control signals
2020-12-29 Move M.2 up to meet component clearance
2020-12-29 Reconnect and route HPM control signals
2020-12-29 Swapped PHY, P-MOSFETs fix
2020-12-29 Rotate FPGA to match BMC PCIe lanes
2020-12-29 Added USB3300 controllers
2020-12-29 Reroute control signals
2020-12-29 Update signal mapping
2020-12-29 Add layout for ULPI USB2
2020-12-30 Add layout for QSPI1
2020-12-30 Add layout for ULPI USB1
2020-12-30 Started routing SGPIO
2020-12-30 Remap DDR3 to B35
2020-12-30 Started DRC fanout
2020-12-30 Replaced and connected eMMC, replaced RJ45
2020-12-30 Connected ethernet
2020-12-30 Update RBIAS and filtering caps around ULPI USB controlers
2020-12-31 DDR routing in progress
2020-12-31 Add DDR signal layout
2020-12-31 Fix swapped signals in QSPI1
2020-12-31 DDR3 expose power pads on vias
2020-12-31 Add filtering caps to DDR
2020-12-31 Route low speed IOs
2020-12-31 Reconnect eMMC, route low speed signals
2021-01-02 Route BMC PCIe
2021-01-02 Break route low I2C
2021-01-03 Route low speed IO towards FPGA
2021-01-04 Connect low speed IOs to FPGA
2021-01-04 Routed I3C signals
2021-01-04 move Flash ICs under RoT
2021-01-04 Fix PCB outline
2021-01-04 Cleaned up power sequencer
2021-01-04 Connected user LEDs
2021-01-04 Updated voltage supply labels, connected gpios left
2021-01-04 Removed JTAG reference
2021-01-04 Typo fix
2021-01-04 Replaced RoT connector with higher one
2021-01-04 README update
2021-01-04 Add component placement
2021-01-04 Updated local libs
2021-01-04 Fixed EN signals 0Rs
2021-01-04 Fixed footprints on PCB
2021-01-04 Add connector cut-out
2021-01-04 Local lib fix
2021-01-04 Local libs fix
2021-01-05 Added power planes, set M.2 mounting hole position
2021-01-05 Added 5V0 plane
2021-01-05 Add JTAG routing
2021-01-05 Add RoT stood
2021-01-05 Add FPGA 100MHz clock source
2021-01-05 Add configuration modes routing
2021-01-06 Route configuration QSPI
2021-01-06 Update DDR3 termination
2021-01-06 minor fixes
2021-01-06 Update schematic notes, update SPI0 connection
2021-01-07 Update filtering capacitors
2021-01-07 Update DDR3 filtering
2021-01-07 Update ETH lanes
2021-01-07 Routed RoT flashes
2021-01-07 Reconnect user LEDs
2021-01-07 Add LEDs routing and oprimize flashes
2021-01-07 Add ethernet traces impedance tuning
2021-01-07 Fix ethernet traces DRC_errors and clock position
2021-01-07 Add 5V and GND routing
2021-01-08 Update layout around filtering caps
2021-01-08 Update layout around DC/dC
2021-01-08 Replaced 1V2 voltage regulator
2021-01-08 Added 1V2 led indicator
2021-01-08 Added 1V2 voltage regulator to PCB, routing
2021-01-08 Generated local libs
2021-01-08 All nets connected
2021-01-08 Cleaned up designators - top
2021-01-08 Cleaned up designators - bottom
2021-01-08 Cleaned up schematics
2021-01-11 Make DRC clean
2021-01-12 Reconnect RGMII clocks to MRCC pins
2021-01-13 Fix 1v0 translator
2021-01-14 Update DDR3 length tunning
2021-01-14 Update length tunning around eMMC
2021-01-18 Add keep-out areas
2021-01-18 Move components from keep-out areas
2021-01-20 Fix unconected DVDDL pin and ETH LED labels
2021-01-20 Clean up designators of moved components
2021-01-20 Add JTAG FTDI to schematic
2021-01-22 Fix LED labels
2021-01-22 Routed FTDI/JTAG
2021-01-23 Update USB 3d model and add VBUS decoupling
2021-01-25 FTDI/JTAG moved out of component keep-out zone
2021-01-25 Add via stitching
2021-01-25 Add logotypes and fix DRC errors
2021-01-25 Bumped revision to 1.0.1 - replaced ROT connector, added ROT signals and connected to FPGA
2021-01-25 Fix DRC errors
2021-01-26 Update edge connector
2021-01-26 Add aux pwr connector
2021-01-26 Reroute x4 PCIe interface
2021-01-27 Fix USB3300 circuit
    -remove 1V8 connection
    -add capacitance at internal 1v8 regulators
    -apply changes to PCB
2021-01-27 Replace pull-up resistors
2021-01-27 Fixed libs
2021-01-27 Fix eMMC pull-ups
2021-01-27 update loclib
2021-01-27 Add pico lock connectors to pcb
2021-01-27 Adjust RoT connector position
2021-01-27 Update TPM Pmod and add connector's designators
2021-01-28 Add delay cap and connect 5V_PG with sequencer enable
2021-01-28 Changed MDC/MDIO pullups. Changed ETH_LEDx polarity
2021-01-28 Updated sequencer circuit
2021-01-28 9774040151
2021-01-28 Fix in 9774025151
2021-01-28 Added ESPI level translator
2021-01-28 Route orphaned signals
2021-01-28 Routed ESPI level shifter
2021-01-29 Connected TPM control signals to FPGA
2021-01-29 Added MEMS generators, updated local libs
2021-01-29 Adjusted USB chips decoupling
2021-01-29 Move I3C translator from bottom layer
2021-01-29 Update DNP fields
2021-01-29 Replace TVS diode
2021-02-01 Fixed PCIe differential pairs widths
2021-02-01 Fix in board design rules
2021-02-01 Reduce redundant blind vias pairs
2021-02-01 Bump release to 1.0.2
2021-02-01 Bump release to 1.0.3
2021-02-01 Update lenght tunning of RGMII
2021-02-01 Rev. 1.0.4 sent to CH
2021-02-03 Production release
2021-03-05 In5-Bot vias changed to TH. Bumped to 1.0.4
2021-03-09 Removed 2 broken tracks
2021-03-16 Changed ETH clock to oscillator. Bumped to 1.0.5
2021-03-29 Change FT2232 into FT4232
2021-03-29 Update layout, DRC clean
2021-03-29 Add spare DBG_UART, DRC clean
2021-03-29 Bump release to 1.0.6
2021-03-29 Minor fix
2021-03-29 Update local libraries
2021-04-02 Moved R68
2021-04-02 Connected VUSB to FTDI's reset
2021-04-02 Exposed copper and large mounting holes
2021-05-03 Update schematics
2021-05-03 LICENSE: add copyrights
2021-05-03 README: Add copyrights
2021-05-17 README: add photo
2021-05-21 upload new diagram
2021-05-21 Add redesigned diagram
2021-06-24 Notes added by 'git notes add'
2021-08-23 Assign DNP to DRAM pullup resistors
2021-08-23 Mark U21 as DNP
2021-10-06 Review / simplify README
2021-10-06 Added some space
2021-10-08 Update photo
2022-05-27 Resize photo
2022-05-27 README: Add badge
2022-09-26 Bump revision to 1.1.0
2022-09-26 Fix I2C5 and PCIE connections on J9 (schematic and library symbol fix)
2022-09-26 Reroute I2C5, PCIE and GND on J9, update footprint
2022-09-28 Update PDF schematics
2022-09-28 Initial conversion to KiCad 6.x format. Checked schematics after conversion. Cleared tracks and vias.
2022-09-29 Checked PCB. Routed one missing track in PROGRAM net. Checked DRC
2022-09-29 Removed KiCad 5.x legacy files
2022-09-29 Corrected all small errors. Fixed 3D model of USB connector
2022-10-21 Start ignoring backups
2022-10-21 Add high-res photos
2023-02-09 Hide M.2 silkscreen outline on mechanical layer
2023-11-06 Introduce component standardization
2023-11-06 Fix schematic ERC errors. ERC clean
2023-11-06 Fix board stackup
2023-11-06 Fix PCB DRC. DRC clean
2023-11-06 Bump revision to 1.1.1
2023-11-07 Add OHP assets

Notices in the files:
parts and their libraries:
Copyright 2016 Accelerated Designs. All rights reserved.
